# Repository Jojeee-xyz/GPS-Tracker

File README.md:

# GPS-Tracker
Project files for a third year university project

## Contents
* Output files stored in GPS-Tracker/Output/ (last generated gerbers, etc)
* Kicad source files stored in the base directory
* Last generated PDFs to be stored in GPS-Tracker/pdfs

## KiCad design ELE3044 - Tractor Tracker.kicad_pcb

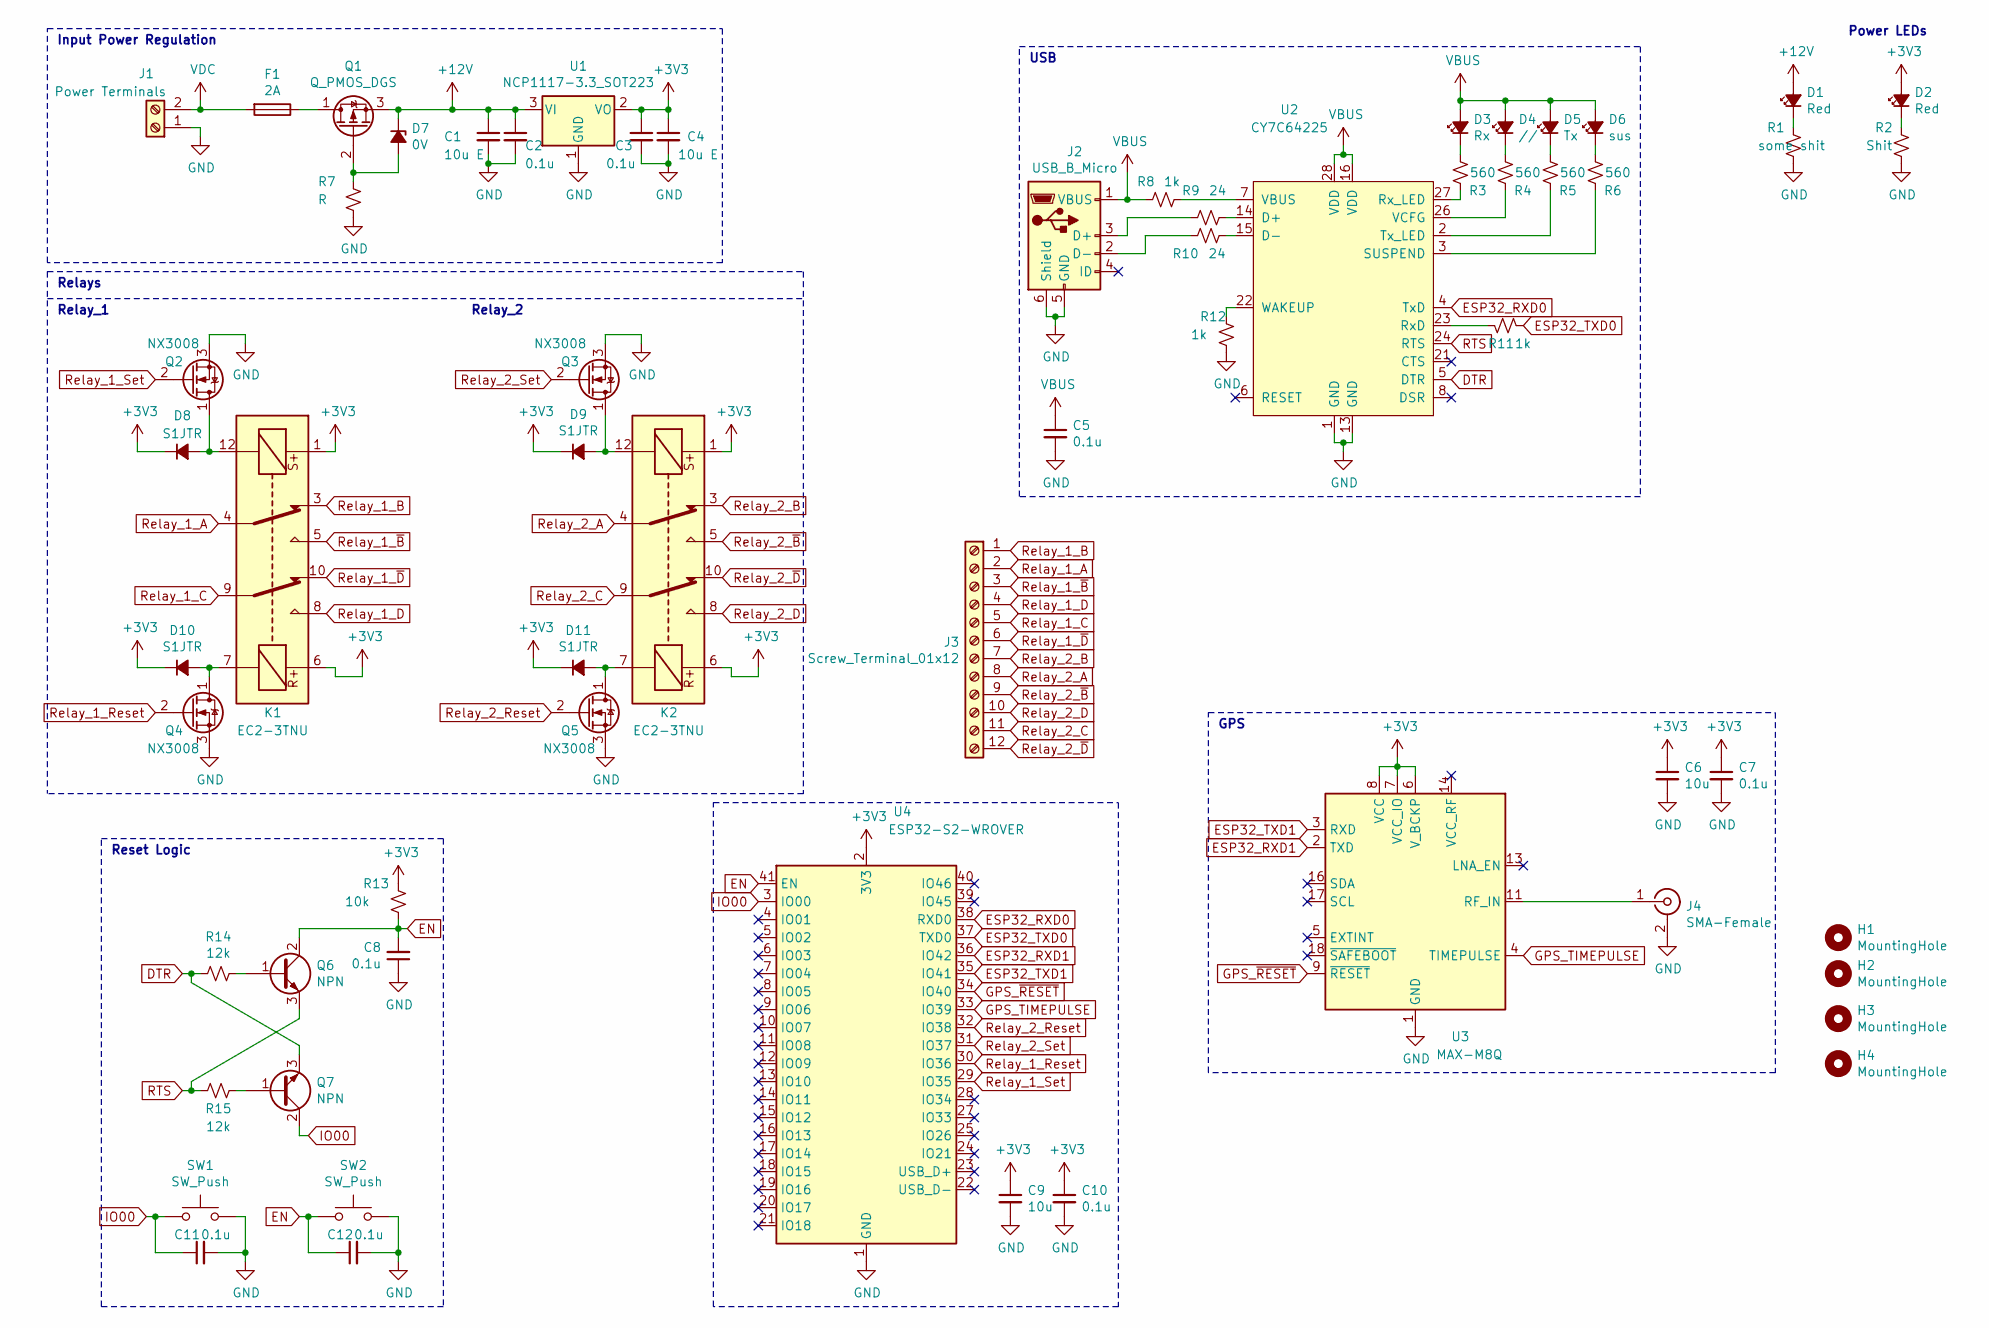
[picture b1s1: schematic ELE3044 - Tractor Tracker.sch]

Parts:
C1, C4: 10u E; CP_Elec_6.3x3.9
C2, C3, C5, C7, C8, C10, C11, C12: 0.1u; C_0805_2012Metric_Pad1.18x1.45mm_HandSolder
C6, C9: 10u; C_0805_2012Metric_Pad1.18x1.45mm_HandSolder
D1, D2: Red; D_0805_2012Metric
D3: Rx; D_0805_2012Metric
D4: //; D_0805_2012Metric
D5: Tx; D_0805_2012Metric
D6: sus; D_0805_2012Metric
D7: 0V; D_SMA_Handsoldering
D8, D9, D10, D11: S1JTR; D_SMB_Handsoldering
F1: 2A; Fuse_1206_3216Metric_Pad1.42x1.75mm_HandSolder
H1, H2, H3, H4: MountingHole; MountingHole_4.3mm_M4
J1: Power Terminals; BarrierBlock_TE_4PCV-02-006_2-pole_P8.26mm
J2: USB_B_Micro; USB_Micro-B_Molex-105017-0001
J3: Screw_Terminal_01x12; BarrierBlock_TE_4PCV-12-006_12-pole_P8.26mm
J4: SMA-Female; SMA_Amphenol_901-144_Vertical
K1, K2: EC2-3TNU; Relay_DPDT_Kemet_EC2_DoubleCoil
Q1: Q_PMOS_DGS; SOT-23-6_Handsoldering
Q2, Q3, Q4, Q5: NX3008; SOT-23
Q6, Q7: NPN; SOT-23
R1: some shit; R_0805_2012Metric_Pad1.20x1.40mm_HandSolder
R2: Shit; R_0805_2012Metric_Pad1.20x1.40mm_HandSolder
R3, R4, R5, R6: 560; R_0805_2012Metric_Pad1.20x1.40mm_HandSolder
R7: R; R_0805_2012Metric_Pad1.20x1.40mm_HandSolder
R8, R11, R12: 1k; R_0805_2012Metric_Pad1.20x1.40mm_HandSolder
R9, R10: 24; R_0805_2012Metric_Pad1.20x1.40mm_HandSolder
R13: 10k; R_0805_2012Metric_Pad1.20x1.40mm_HandSolder
R14, R15: 12k; R_0805_2012Metric_Pad1.20x1.40mm_HandSolder
SW1, SW2: SW_Push; SW_Push_1P1T_NO_6x6mm_H9.5mm
U1: NCP1117-3.3_SOT223; SOT-223
U2: CY7C64225; SSOP-28_5.3x10.2mm_P0.65mm
U3: MAX-M8Q; ublox_MAX
U4: ESP32-S2-WROVER

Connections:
+3V3: C3.1, C4.1, C6.1, C7.1, C9.1, C10.1, D2.2 (A), D8.1 (K), D9.1 (K), D10.1 (K), D11.1 (K), K1.1, K1.6, K2.1, K2.6, R13.1, U1.2 (VO), U3.6 (V_BCKP), U3.7 (VCC_IO), U3.8 (VCC), U4.2 (3V3)
+12V: C1.1, C2.1, D1.2 (A), D7.1 (K), Q1.3 (S), U1.3 (VI)
DTR: Q7.3 (E), R14.2, U2.5 (DTR)
EN: C8.2, C12.1, Q6.2 (C), R13.2, SW2.1, U4.41 (EN)
ESP32_RXD0: U2.4 (TxD), U4.38 (RXD0)
ESP32_RXD1: U3.2 (TXD), U4.36 (IO42)
ESP32_TXD0: R11.1, U4.37 (TXD0)
ESP32_TXD1: U3.3 (RXD), U4.35 (IO41)
GND: C1.2, C2.2, C3.2, C4.2, C5.2, C6.2, C7.2, C8.1, C9.2, C10.2, C11.2, C12.2, J1.1, J2.5 (GND), J2.6 (Shield), J4.2 (Ext), Q2.3 (S), Q3.3 (S), Q4.3 (S), Q5.3 (S), R1.2, R2.2, R7.2, R12.2, SW1.2, SW2.2, U1.1 (GND), U2.1 (GND), U2.13 (GND), U3.1 (GND), U3.10 (GND), U3.12 (GND), U4.1 (GND), U4.26 (GND), U4.42 (GND), U4.43 (GND)
GPS_TIMEPULSE: U3.4 (TIMEPULSE), U4.33 (IO39)
GPS_~RESET: U3.9 (~RESET), U4.34 (IO40)
IO00: C11.1, Q7.2 (C), SW1.1, U4.3 (IO00)
unnamed: D1.1 (K), R1.1
unnamed: D2.1 (K), R2.1
unnamed: D3.1 (K), R3.2
unnamed: D4.1 (K), R4.2
unnamed: D5.1 (K), R5.2
unnamed: D6.1 (K), R6.2
unnamed: D7.2 (A), Q1.2 (G), R7.1
unnamed: D8.2 (A), K1.12, Q2.1 (D)
unnamed: D9.2 (A), K2.12, Q3.1 (D)
unnamed: D10.2 (A), K1.7, Q4.1 (D)
unnamed: D11.2 (A), K2.7, Q5.1 (D)
unnamed: F1.1, Q1.1 (D)
unnamed: J2.2 (D-), R10.1
unnamed: J2.3 (D+), R9.2
unnamed: J4.1 (In), U3.11 (RF_IN)
unnamed: Q6.1 (B), R14.1
unnamed: Q7.1 (B), R15.1
unnamed: R3.1, U2.27 (Rx_LED)
unnamed: R4.1, U2.26 (VCFG)
unnamed: R5.1, U2.2 (Tx_LED)
unnamed: R6.1, U2.3 (SUSPEND)
unnamed: R8.1, U2.7 (VBUS)
unnamed: R9.1, U2.14 (D+)
unnamed: R10.2, U2.15 (D-)
unnamed: R11.2, U2.23 (RxD)
unnamed: R12.1, U2.22 (WAKEUP)
RTS: Q6.3 (E), R15.2, U2.24 (RTS)
Relay_1_A: J3.2, K1.4
Relay_1_B: J3.1, K1.3
Relay_1_C: J3.5, K1.9
Relay_1_D: J3.4, K1.8
Relay_1_Reset: Q4.2 (G), U4.30 (IO36)
Relay_1_Set: Q2.2 (G), U4.29 (IO35)
Relay_1_~B: J3.3, K1.5
Relay_1_~D: J3.6, K1.10
Relay_2_A: J3.8, K2.4
Relay_2_B: J3.7, K2.3
Relay_2_C: J3.11, K2.9
Relay_2_D: J3.10, K2.8
Relay_2_Reset: Q5.2 (G), U4.32 (IO38)
Relay_2_Set: Q3.2 (G), U4.31 (IO37)
Relay_2_~B: J3.9, K2.5
Relay_2_~D: J3.12, K2.10
VBUS: C5.1, D3.2 (A), D4.2 (A), D5.2 (A), D6.2 (A), J2.1 (VBUS), R8.2, U2.16 (VDD), U2.28 (VDD)
VDC: F1.2, J1.2

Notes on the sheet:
GPS
Power LEDs
Input Power Regulation
USB
Relay_2
Relay_1
Relays
Reset Logic

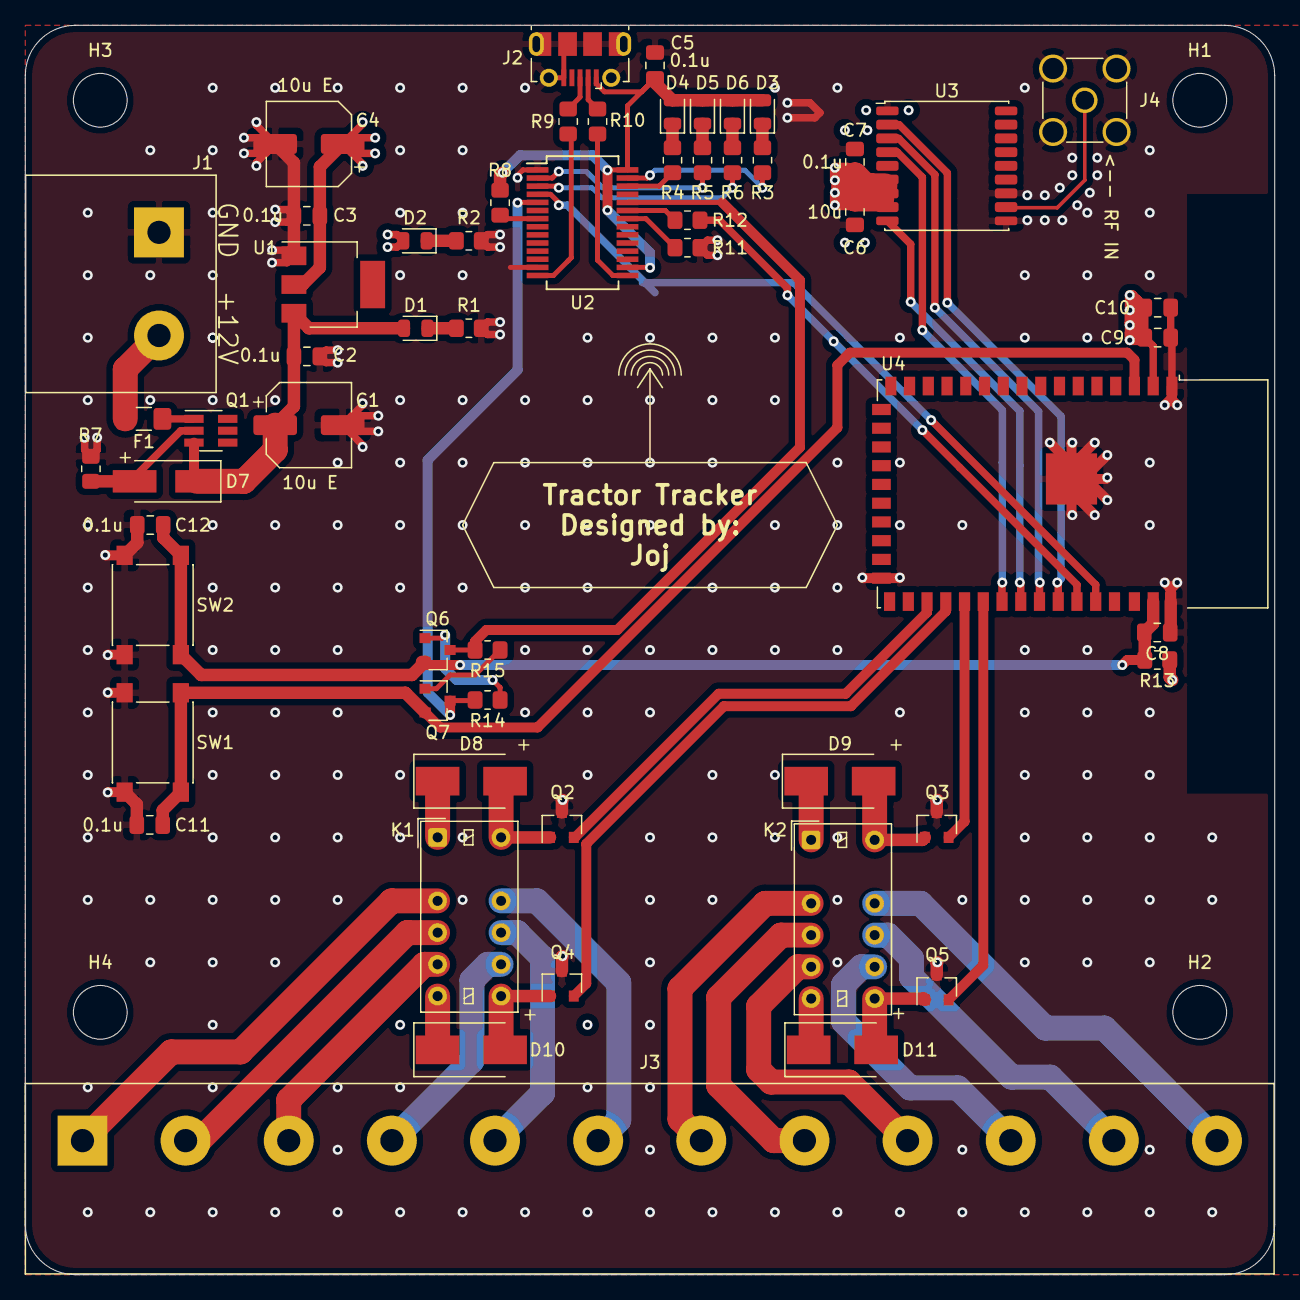
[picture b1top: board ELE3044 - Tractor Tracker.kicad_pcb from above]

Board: 4 copper layers, 100.0 x 100.0 mm, 62 parts (0 on the bottom side), 57 nets.

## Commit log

2021-12-02 Revert "First commit"
    This reverts commit e8cb366e3254d9f06bc7109d3ad26a2ef2db6d74.
2021-12-02 Revert "Revert "First commit""
    This reverts commit aca9da2123c8ff5d6d65e58e942f8d5a20036329.
2021-12-02 Fixed .gitignore
2021-12-02 .gitignore is now working
2021-12-02 Added new output files, a render image and PDF schematic
